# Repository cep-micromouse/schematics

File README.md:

# schematics
Schematics for Chuck

## KiCad setup
- Add the libraries in `libs/` to the project in `Preferences/Manage Symbol Libraries...`

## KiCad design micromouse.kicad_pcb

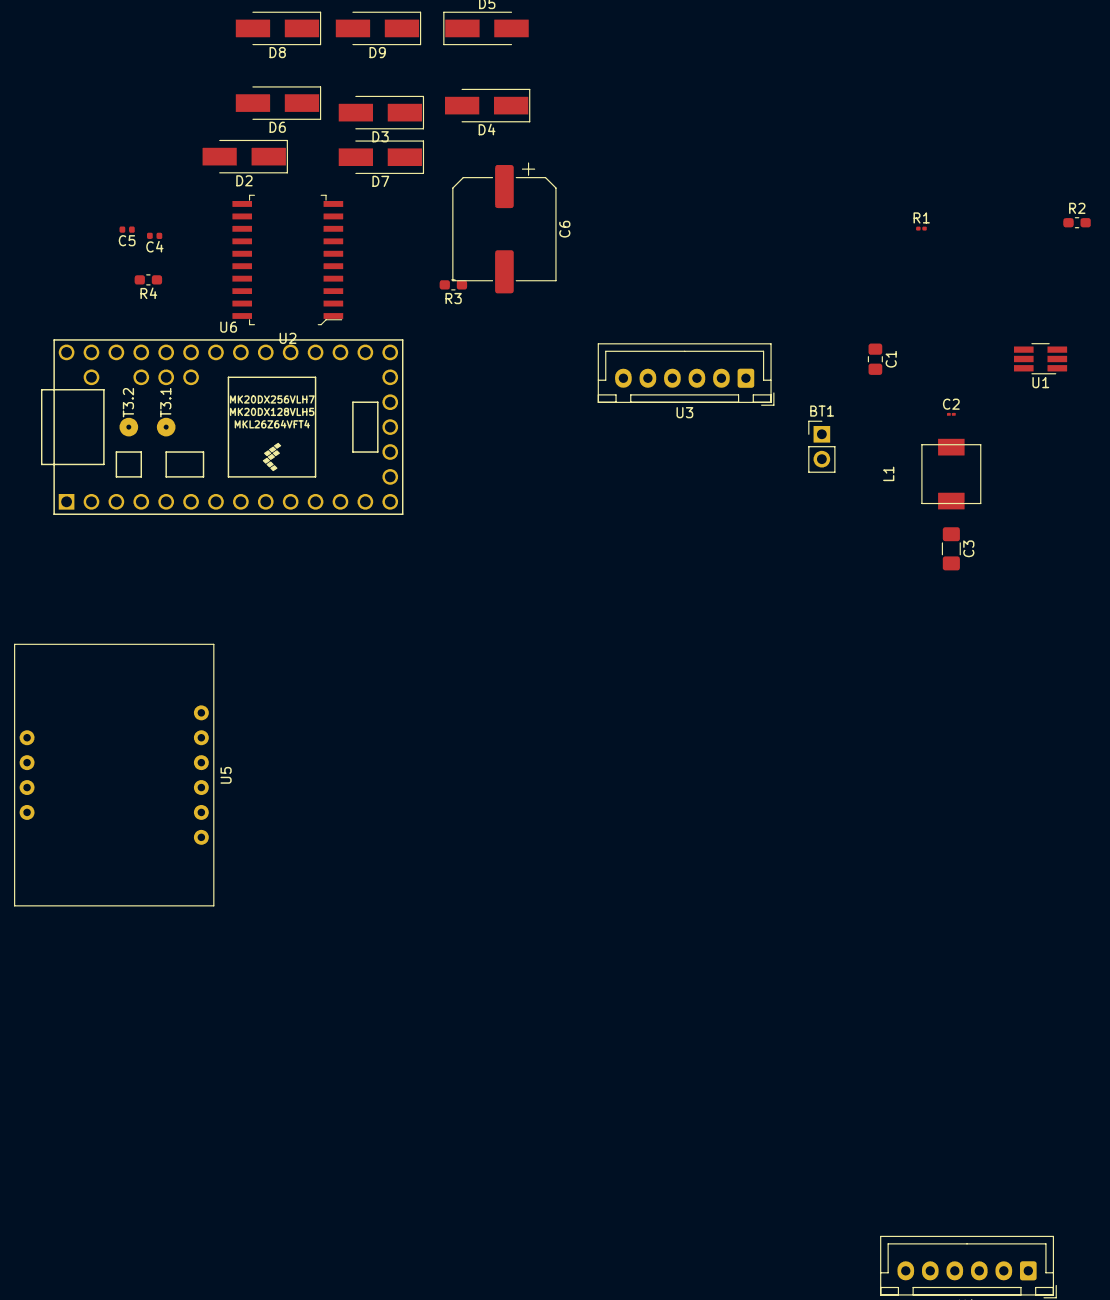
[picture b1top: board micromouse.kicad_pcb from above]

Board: 2 copper layers, 28 parts (0 on the bottom side), 15 nets, no tracks yet.

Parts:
BT1: Battery; PinHeader_1x02_P2.54mm_Vertical
C1: 10uF; C_0805_2012Metric_Pad1.15x1.40mm_HandSolder
C2: 0.1uF; C_01005_0402Metric
C3: 47uF; C_1206_3216Metric_Pad1.42x1.75mm_HandSolder
C4, C5: 0.1uF; C_0402_1005Metric
C6: 200uF; CP_Elec_10x7.9
D2, D3, D4, D5, D6, D7, D8, D9: B120B; D_SMA_Handsoldering
L1: 4.7uH; B82462A4
M1, M2: Motor_DC; Motor
R1: 56.2kΩ; R_0201_0603Metric
R2, R3, R4: 10kΩ; R_0603_1608Metric_Pad1.05x0.95mm_HandSolder
U1: TPS561201; TSOT-23-6_HandSoldering
U2: L298P; SOIC-20_W7.5mm
U3, U4: Encoder; JST_XH_B6B-XH-A_1x06_P2.50mm_Vertical
U5: BNO055
U6: Teensy3.2; Teensy30_31_32_LC

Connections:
+5V: C3.1, C4.1, L1.2, R1.2, U2.12, U3.4, U4.4, U5.5, U6.33
+VDC: BT1.1, C1.1, U1.3, U1.5
/motors/ENABLE_A: R3.2, U2.8
/motors/ENABLE_B: R4.1, U2.14
GND: BT1.2, C1.2, C3.2, C4.2, C5.2, C6.2, D2.2, D4.2, D6.2, D8.2, R2.2, R3.1, R4.2, U1.1, U2.1, U2.10, U2.11, U2.20, U3.1, U4.1, U5.7, U6.1
unnamed: C2.1, L1.1, U1.6
unnamed: C2.2, U1.2
unnamed: D2.1, D3.2, U2.4
unnamed: D4.1, D5.2, U2.5
unnamed: D6.1, D7.2, U2.16
unnamed: D8.1, D9.2, U2.17
unnamed: R1.1, R2.1, U1.4
unnamed: U5.8, U6.25
unnamed: U5.9, U6.26
VDC: C5.1, C6.1, D3.1, D5.1, D7.1, D9.1, U2.6

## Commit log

2019-09-06 Add initial power schematic
2019-09-06 Finish bulk of motor driver
2019-09-08 Move blocks to seperate sheets
2019-09-09 Add encoder, distance sensor, and gyro
2019-09-18 Add libraries, annotate components
2019-10-30 update schematic
